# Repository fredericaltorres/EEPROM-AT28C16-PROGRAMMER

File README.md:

# EEPROM-AT28C16-PROGRAMMER

EEPROM AT28C16 PROGRAMMER using an Arduino Mega

See [Blog](http://frederictorres.blogspot.com/2018/06/at28c16-eeprom-programmer.html)

# Copyright
Copyright Frederic Torres 2018

# License
MIT License

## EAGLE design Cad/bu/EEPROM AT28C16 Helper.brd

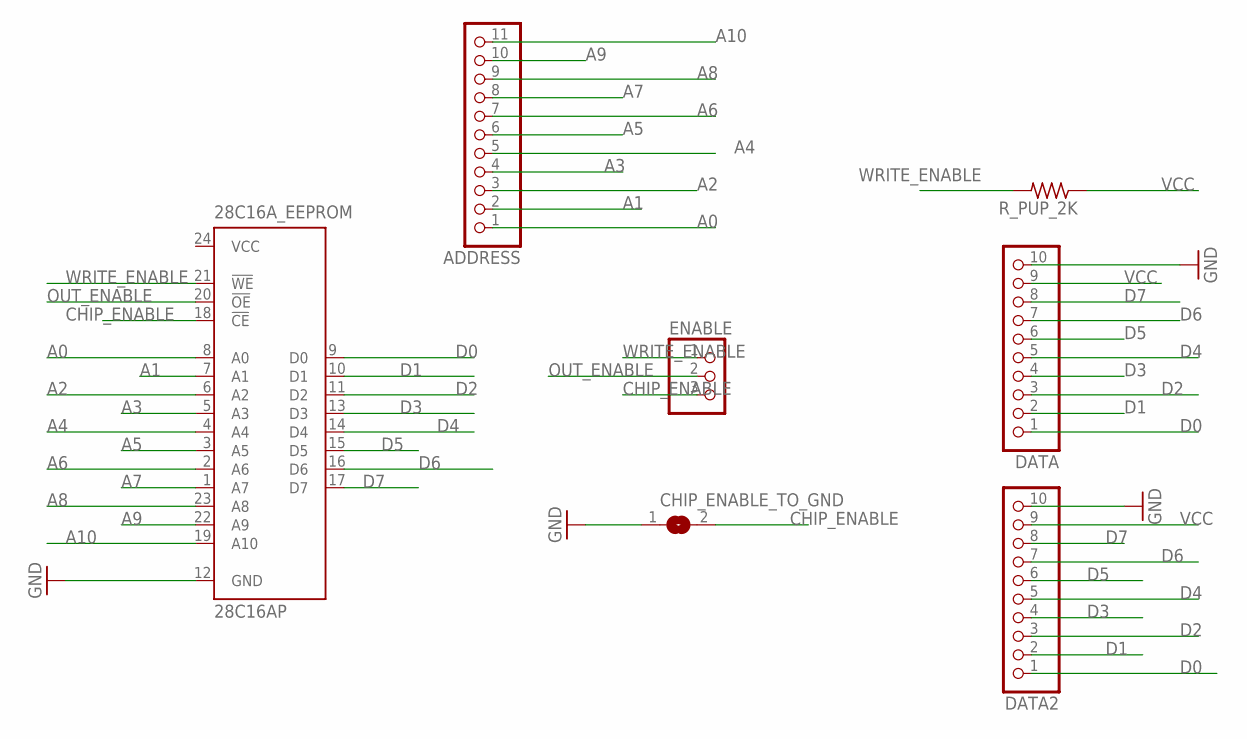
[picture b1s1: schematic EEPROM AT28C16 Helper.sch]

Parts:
28C16A_EEPROM: 28C16AP; DIL24-6
ADDRESS: PINHD-1X11; 1X11
CHIP_ENABLE_TO_GND: SOLDERJUMPERREFLOW; SOLDERJUMPER_REFLOW
DATA, DATA2: PINHD-1X10; 1X10-BIG
ENABLE: PINHD-1X3; 1X03
R_PUP_2K: R-US_R1206; R1206

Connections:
A0: 28C16A_EEPROM.8 (A0), ADDRESS.1
A1: 28C16A_EEPROM.7 (A1), ADDRESS.2
A2: 28C16A_EEPROM.6 (A2), ADDRESS.3
A3: 28C16A_EEPROM.5 (A3), ADDRESS.4
A4: 28C16A_EEPROM.4 (A4), ADDRESS.5
A5: 28C16A_EEPROM.3 (A5), ADDRESS.6
A6: 28C16A_EEPROM.2 (A6), ADDRESS.7
A7: 28C16A_EEPROM.1 (A7), ADDRESS.8
A8: 28C16A_EEPROM.23 (A8), ADDRESS.9
A9: 28C16A_EEPROM.22 (A9), ADDRESS.10
A10: 28C16A_EEPROM.19 (A10), ADDRESS.11
CHIP_ENABLE: 28C16A_EEPROM.18 (!CE), CHIP_ENABLE_TO_GND.2, ENABLE.3
D0: 28C16A_EEPROM.9 (D0), DATA.1, DATA2.1
D1: 28C16A_EEPROM.10 (D1), DATA.2, DATA2.2
D2: 28C16A_EEPROM.11 (D2), DATA.3, DATA2.3
D3: 28C16A_EEPROM.13 (D3), DATA.4, DATA2.4
D4: 28C16A_EEPROM.14 (D4), DATA.5, DATA2.5
D5: 28C16A_EEPROM.15 (D5), DATA.6, DATA2.6
D6: 28C16A_EEPROM.16 (D6), DATA.7, DATA2.7
D7: 28C16A_EEPROM.17 (D7), DATA.8, DATA2.8
GND: 28C16A_EEPROM.12 (GND), CHIP_ENABLE_TO_GND.1, DATA.10, DATA2.10
OUT_ENABLE: 28C16A_EEPROM.20 (!OE), ENABLE.2
VCC: 28C16A_EEPROM.24 (VCC), DATA.9, DATA2.9, R_PUP_2K.1
WRITE_ENABLE: 28C16A_EEPROM.21 (!WE), ENABLE.1, R_PUP_2K.2

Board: 2 copper layers, 7 parts (0 on the bottom side), 24 nets, no tracks yet.

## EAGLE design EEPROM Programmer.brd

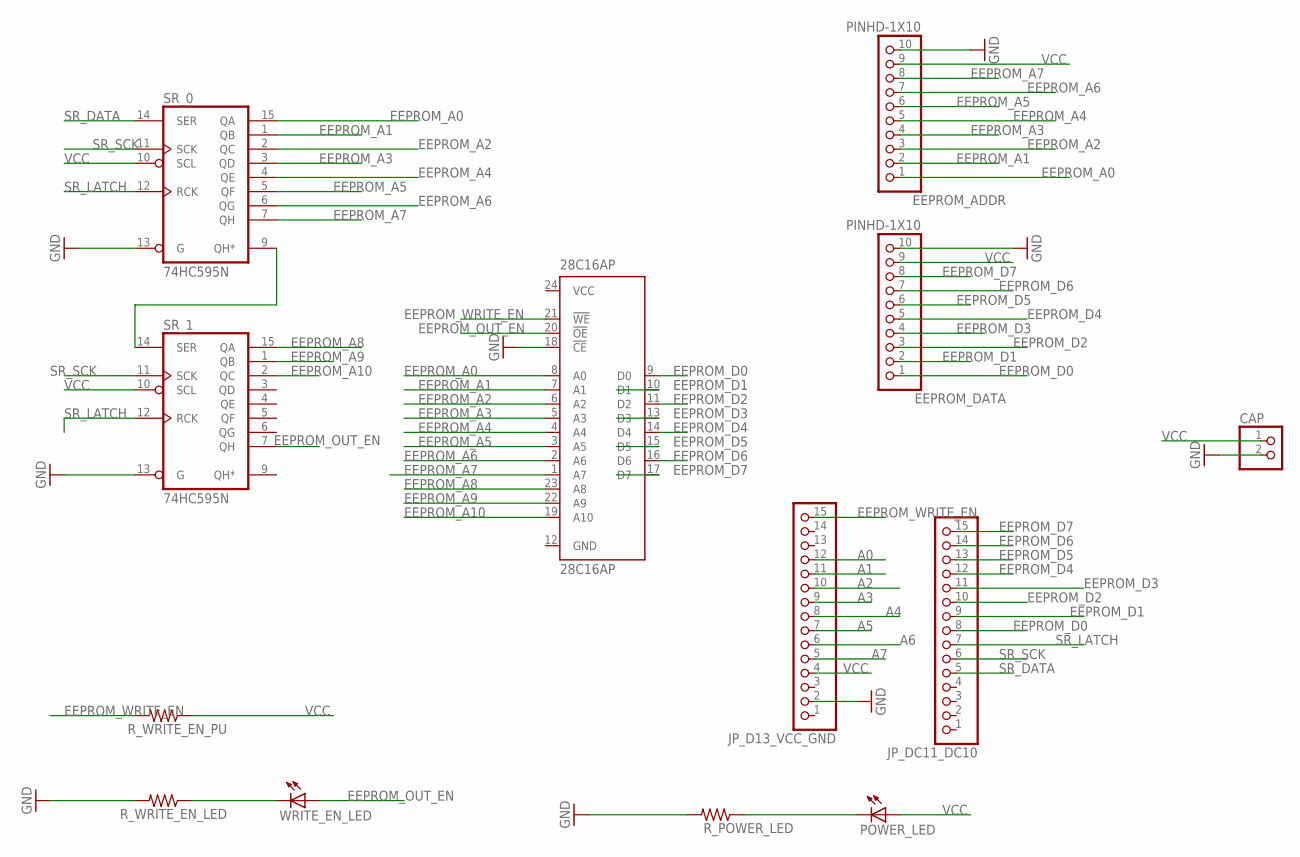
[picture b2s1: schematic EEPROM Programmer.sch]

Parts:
28C16AP: 28C16AP; DIL24-6
CAP: PINHD-1X2; 1X02
EEPROM_ADDR: PINHD-1X10; 1X10-BIG
EEPROM_DATA: PINHD-1X10; 1X10-BIG
JP_D13_VCC_GND: PINHD-1X15; 1X15
JP_DC11_DC10: PINHD-1X15; 1X15
POWER_LED: LEDSMT1206; 1206
R_POWER_LED: R-US_R1206; R1206
R_WRITE_EN_LED: R-US_R1206; R1206
R_WRITE_EN_PU: R-US_R1206; R1206
SR_0, SR_1: 74HC595N; DIL16
WRITE_EN_LED: LEDSMT1206; 1206

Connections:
A0: JP_D13_VCC_GND.12
A1: JP_D13_VCC_GND.11
A2: JP_D13_VCC_GND.10
A3: JP_D13_VCC_GND.9
A4: JP_D13_VCC_GND.8
A5: JP_D13_VCC_GND.7
A6: JP_D13_VCC_GND.6
A7: JP_D13_VCC_GND.5
EEPROM_A0: 28C16AP.8 (A0), EEPROM_ADDR.1, SR_0.15 (QA)
EEPROM_A1: 28C16AP.7 (A1), EEPROM_ADDR.2, SR_0.1 (QB)
EEPROM_A2: 28C16AP.6 (A2), EEPROM_ADDR.3, SR_0.2 (QC)
EEPROM_A3: 28C16AP.5 (A3), EEPROM_ADDR.4, SR_0.3 (QD)
EEPROM_A4: 28C16AP.4 (A4), EEPROM_ADDR.5, SR_0.4 (QE)
EEPROM_A5: 28C16AP.3 (A5), EEPROM_ADDR.6, SR_0.5 (QF)
EEPROM_A6: 28C16AP.2 (A6), EEPROM_ADDR.7, SR_0.6 (QG)
EEPROM_A7: 28C16AP.1 (A7), EEPROM_ADDR.8, SR_0.7 (QH)
EEPROM_A8: 28C16AP.23 (A8), SR_1.15 (QA)
EEPROM_A9: 28C16AP.22 (A9), SR_1.1 (QB)
EEPROM_A10: 28C16AP.19 (A10), SR_1.2 (QC)
EEPROM_D0: 28C16AP.9 (D0), EEPROM_DATA.1, JP_DC11_DC10.8
EEPROM_D1: 28C16AP.10 (D1), EEPROM_DATA.2, JP_DC11_DC10.9
EEPROM_D2: 28C16AP.11 (D2), EEPROM_DATA.3, JP_DC11_DC10.10
EEPROM_D3: 28C16AP.13 (D3), EEPROM_DATA.4, JP_DC11_DC10.11
EEPROM_D4: 28C16AP.14 (D4), EEPROM_DATA.5, JP_DC11_DC10.12
EEPROM_D5: 28C16AP.15 (D5), EEPROM_DATA.6, JP_DC11_DC10.13
EEPROM_D6: 28C16AP.16 (D6), EEPROM_DATA.7, JP_DC11_DC10.14
EEPROM_D7: 28C16AP.17 (D7), EEPROM_DATA.8, JP_DC11_DC10.15
EEPROM_OUT_EN: 28C16AP.20 (!OE), SR_1.7 (QH), WRITE_EN_LED.A
EEPROM_WRITE_EN: 28C16AP.21 (!WE), JP_D13_VCC_GND.15, R_WRITE_EN_PU.2
GND: 28C16AP.12 (GND), 28C16AP.18 (!CE), CAP.2, EEPROM_ADDR.10, EEPROM_DATA.10, JP_D13_VCC_GND.2, R_POWER_LED.2, R_WRITE_EN_LED.2, SR_0.8 (GND), SR_0.13 (G), SR_1.8 (GND), SR_1.13 (G)
unnamed: POWER_LED.C, R_POWER_LED.1
unnamed: R_WRITE_EN_LED.1, WRITE_EN_LED.C
unnamed: SR_0.9 (QH*), SR_1.14 (SER)
SR_DATA: JP_DC11_DC10.5, SR_0.14 (SER)
SR_LATCH: JP_DC11_DC10.7, SR_0.12 (RCK), SR_1.12 (RCK)
SR_SCK: JP_DC11_DC10.6, SR_0.11 (SCK), SR_1.11 (SCK)
VCC: 28C16AP.24 (VCC), CAP.1, EEPROM_ADDR.9, EEPROM_DATA.9, JP_D13_VCC_GND.4, POWER_LED.A, R_WRITE_EN_PU.1, SR_0.10 (SCL), SR_0.16 (VCC), SR_1.10 (SCL), SR_1.16 (VCC)

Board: 2 copper layers, 13 parts (0 on the bottom side), 29 nets, no tracks yet.

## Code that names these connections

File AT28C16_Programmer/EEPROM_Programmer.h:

/*
AT28C16 EEPROM Programmer
(C) Frederic Torres 2018
*/

#ifndef _EEPROM_PROGRAMMER_h
#define _EEPROM_PROGRAMMER_h

#if defined(ARDUINO) && ARDUINO >= 100
#include "arduino.h"
#else
#include "WProgram.h"
#endif

#include <fArduino.h>

// Need Arduino Mega 2560

#define EEPROM_D0 2
#define EEPROM_D7 9

#define EEPROM_A0 22
#define EEPROM_A7 29

#define EEPROM_OUTPUT_ENABLE 40
#define EEPROM_WRITE_ENABLE 41

enum DATA_MODE { READ = 0, WRITE };

class EEPROM_Programmer {

private:
	DATA_MODE _dataMode;

public:
	byte DataValue;
	int AddrValue;

	EEPROM_Programmer();
	~EEPROM_Programmer();
	void Init();

	void SetPinsForDataBusInReadMode();
	void SetPinsForDataBusInWriteMode();
	void SetPinsForAddressBus8Bits();

	String GetStatus();
	void SetDataBusWriteData(byte d);
	byte GetDataBusReadData();
	void CheckForReadMode();
	void CheckForWriteMode();

	
	void SetAddressBus8bits(byte addr8bit);
	void SetDataBusAndAddressBus8bitWriteData(byte data, byte addr);

	void AnimationStartSequence();
	void AnimationWorkProperlySequence();
	//#define EEPROM_OUTPUT_ENABLE 40
	//#define EEPROM_WRITE_ENABLE 41
	void SetOutputEnable();
	void SetOutputDisable();
	void InitiateWriteByteOperation();
};

#endif

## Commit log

2018-06-23 Creation
2018-06-23 Some code and schematic
2018-06-23 Update cad images
2018-06-23 Cleaning old code
2018-06-23 Clean code
2018-07-13 Update code now that we have the eeprom programmer board
2018-07-15 Make the programmer works, not yet
2018-07-15 Make the programmer works, working but it seems that my set of EEPROMs are not all good
2018-07-20 added blog link

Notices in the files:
parts and their libraries:
microbuilder: This work is placed in the public domain, and may be freely used for commercial and non-commercial work with the following conditions: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
